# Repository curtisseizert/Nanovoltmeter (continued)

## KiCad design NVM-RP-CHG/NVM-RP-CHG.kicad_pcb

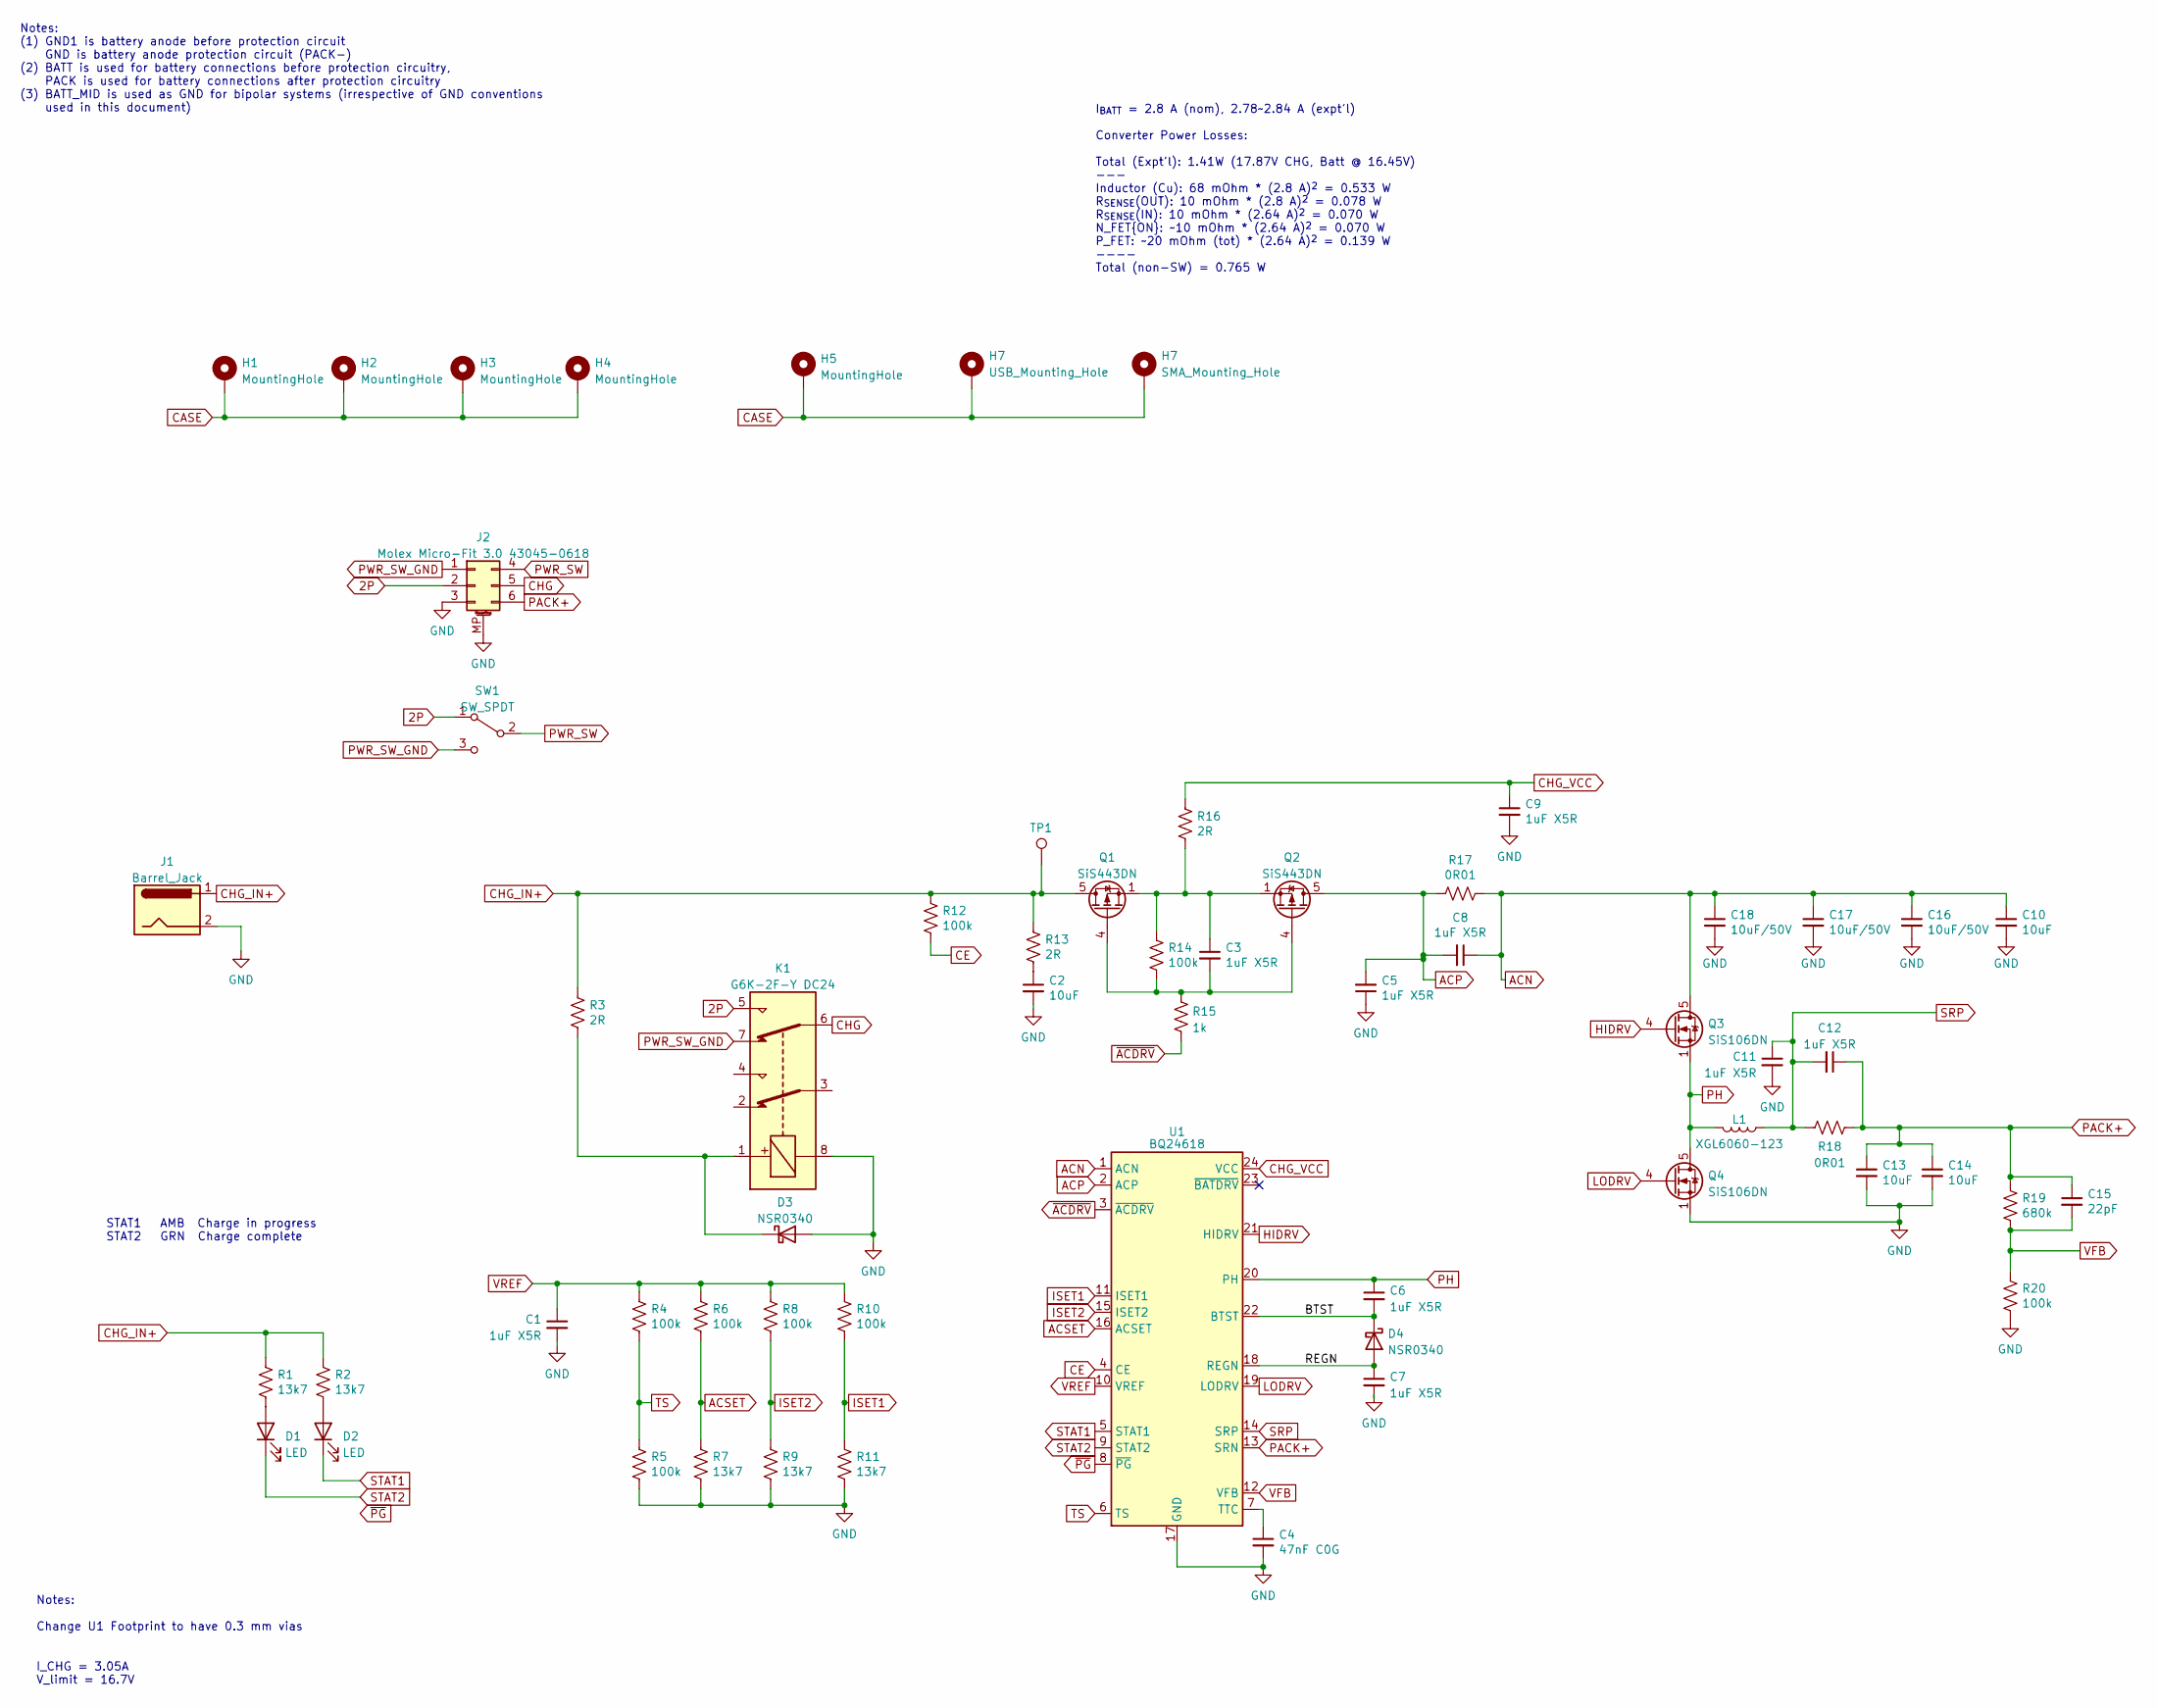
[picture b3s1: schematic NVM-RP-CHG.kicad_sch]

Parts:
C1, C3, C5, C6, C7, C8, C9, C11, C12: 1uF X5R; C_0402_1005Metric
C2, C10, C13, C14: 10uF; C_1206_3216Metric_Red
C4: 47nF C0G; C_0805_2012Metric_Red_outline
C15: 22pF; C_0402_1005Metric
C16, C17, C18: 10uF/50V; C_0805_2012Metric_Red_outline
D1, D2: LED; LED_Osram_Lx_P47F_D2mm_ReverseMount
D3, D4: NSR0340; D_SOD-523
H1, H2, H3, H4: MountingHole; MountingHole_4.3mm_M4_ISO14580_Pad
H5: MountingHole; PanelCutout_6.5mm_PTH
H7: USB_Mounting_Hole; PANEL_CUTOUT_MUSBK15230
J1: Barrel_Jack; BarrelJackDC_Switchcraft721_712
J2: Molex Micro-Fit 3.0 43045-0618; Molex_Micro-Fit_3.0_43045-0618_2x03-1MP_P3.00mm_Vertical
K1: G6K-2F-Y DC24; Relay_DPDT_Omron_G6K-2F-Y
L1: XGL6060-123; L_Coilcraft_XAL60xx_6.36x6.56mm
Q1, Q2: SiS443DN; Vishay_PowerPAK_1212-8_Single
Q3, Q4: SiS106DN; Vishay_PowerPAK_1212-8_Single
R1, R2, R7, R9, R11: 13k7; R_0402_1005Metric
R3, R13, R16: 2R; R_0603_1608Metric_red
R4, R5, R6, R8, R10, R12, R14, R20: 100k; R_0402_1005Metric
R15: 1k; R_0402_1005Metric
R17, R18: 0R01; R_1206_3216Metric
R19: 680k; R_0402_1005Metric
SW1: SW_SPDT; TestPoint_3Pads
TP1: TestPoint; TestPoint_Pad_D1.0mm
U1: BQ24618; HVQFN-24-1EP_4x4mm_P0.5mm_EP2.5x2.5mm

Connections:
2P: J2.2, K1.5, SW1.1 (A)
/BTST: C6.2, D4.1 (K), U1.22 (BTST)
/REGN: C7.1, D4.2 (A), U1.18 (REGN)
ACN: C8.1, C10.1, C16.1, C17.1, C18.1, Q3.5 (D), R17.1, U1.1 (ACN)
ACP: C5.2, C8.2, Q2.5 (D), R17.2, U1.2 (ACP)
ACSET: R6.2, R7.1, U1.16 (ACSET)
CASE: H1.1, H2.1, H3.1, H4.1, H5.1, H7.1; also elsewhere on the board
CE: R12.2, U1.4 (CE)
CHG: J2.5, K1.6
CHG_IN+: J1.1, Q1.5 (D), R1.1, R2.1, R3.2, R12.1, R13.1, TP1.1
CHG_VCC: C9.1, R16.2, U1.24 (VCC)
GND: C1.2, C2.2, C4.2, C5.1, C7.2, C9.2, C10.2, C11.2, C13.2, C14.2, C16.2, C17.2, C18.2, D3.2 (A), J1.2, J2.3, J2.MP (MountPin), K1.8, Q4.1 (S), Q4.2 (S), Q4.3 (S), R5.2, R7.2, R9.2, R11.2, R20.1, U1.17 (GND), U1.25 (EP)
HIDRV: Q3.4 (G), U1.21 (HIDRV)
ISET1: R10.2, R11.1, U1.11 (ISET1)
ISET2: R8.2, R9.1, U1.15 (ISET2)
LODRV: Q4.4 (G), U1.19 (LODRV)
unnamed: C2.1, R13.2
unnamed: C3.1, Q1.1 (S), Q1.2 (S), Q1.3 (S), Q2.1 (S), Q2.2 (S), Q2.3 (S), R14.1, R16.1
unnamed: D1.2 (A), R1.2
unnamed: D2.2 (A), R2.2
unnamed: D3.1 (K), K1.1, R3.1
unnamed: C3.2, Q1.4 (G), Q2.4 (G), R14.2, R15.1
unnamed: C4.1, U1.7 (TTC)
PACK+: C12.1, C13.1, C14.1, C15.1, J2.6, R18.1, R19.2, U1.13 (SRN)
PH: C6.1, L1.2, Q3.1 (S), Q3.2 (S), Q3.3 (S), Q4.5 (D), U1.20 (PH)
PWR_SW: J2.4, SW1.2 (B)
PWR_SW_GND: J2.1, K1.7, SW1.3 (C)
SRP: C11.1, C12.2, L1.1, R18.2, U1.14 (SRP)
STAT1: D2.1 (K), U1.5 (STAT1)
STAT2: D1.1 (K), U1.9 (STAT2)
TS: R4.2, R5.1, U1.6 (TS)
VFB: C15.2, R19.1, R20.2, U1.12 (VFB)
VREF: C1.1, R4.1, R6.1, R8.1, R10.1, U1.10 (VREF)
~ACDRV: R15.2, U1.3 (~ACDRV)
~PG: U1.8 (~PG)

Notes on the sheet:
I_{BATT} = 2.8 A (nom), 2.78~2.84 A (expt'l) Converter Power Losses: Total (Expt'l): 1.41W (17.87V CHG, Batt @ 16.45V) --- Inductor (Cu): 68 mOhm * (2.8 A)^{2} = 0.533 W R_{SENSE}(OUT): 10 mOhm * (2.8 A)^{2} = 0.078 W R_{SENSE}(IN): 10 mOhm * (2.64 A)^{2} = 0.070 W N_FET{ON}: ~10 mOhm * (2.64 A)^{2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
I_CHG = 3.05A V_limit = 16.7V
Notes: (1) GND1 is battery anode before protection circuit GND is battery anode protection circuit (PACK-) (2) BATT is used for battery connections before protection circuitry, PACK is used for battery connections after protection circuitry (3) BATT_MID is used as GND for bipolar systems (irrespect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
STAT1 AMB Charge in progress STAT2 GRN Charge complete
Notes: Change U1 Footprint to have 0.3 mm vias

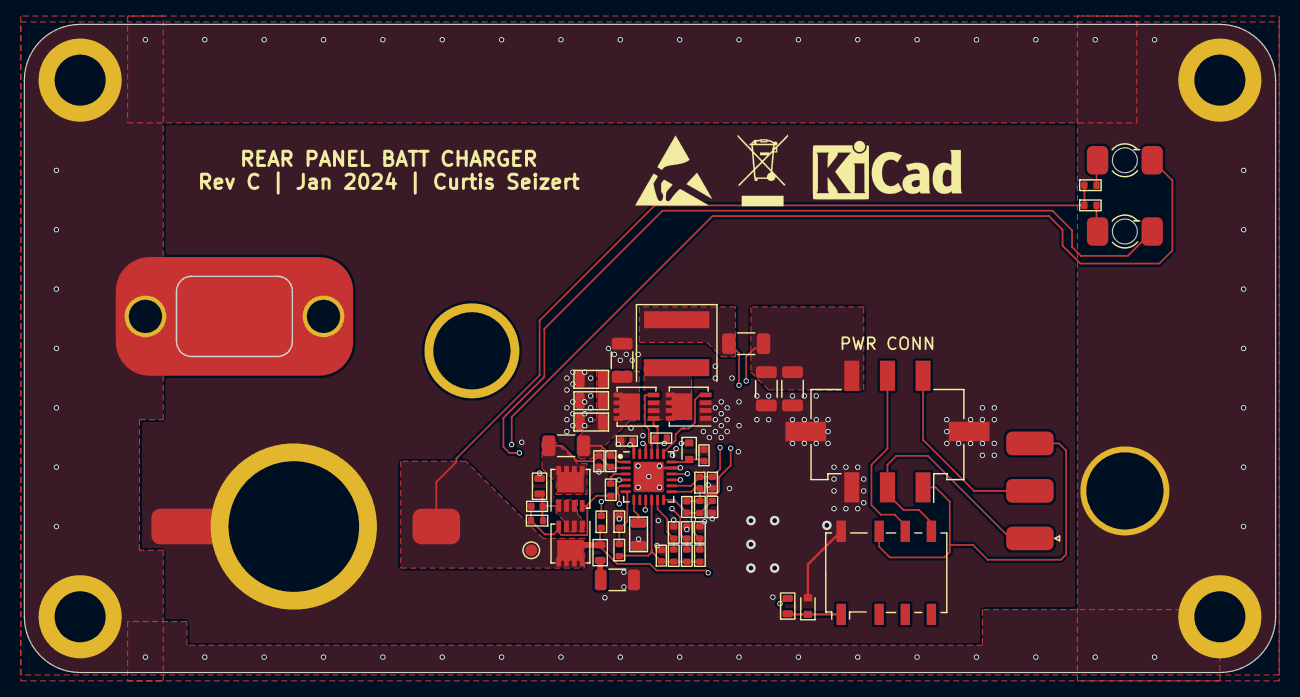
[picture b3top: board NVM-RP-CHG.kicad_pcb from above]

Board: 4 copper layers, 105.4 x 54.6 mm, 60 parts (0 on the bottom side), 34 nets.

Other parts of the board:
H6: USB_Mounting_Hole; PANEL_CUTOUT_MUSBK15230

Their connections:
CASE: H6.1; also elsewhere on the board

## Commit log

2024-01-30 Initial commit of kicad design files
2024-01-30 Update README.md
    Added description
2024-01-30 Added battery design files
2024-02-19 Update README.md
    Added current status section
2024-04-03 Update README.md
    Added principle of operation and some results from testing the board.
2024-04-03 Added FW source files
2024-04-17 Update README.md
    Expanded the principle of operation section and added a simplified schematic.
2024-05-21 Add files via upload
    Rewrote firmware and implemented new features, such as FIFOs for readings and serial inputs, an improved command parser, and better use of DMA/global interrupts to improve performance.
2024-05-21 Update README.md
    Updated current status
2024-05-22 Fixed ADC read timing issues and added commands
2025-08-30 Update README.md
    Added more experimental results and observations, included updated status and plans for next revision
2025-08-30 Update README.md
    Fixed formatting issues
